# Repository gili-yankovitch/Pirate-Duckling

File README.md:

# Pirate-Duckling
Pirate Duckling is an ATTiny85 based Rubber Ducky clone. It is built with absolute minimal components in mind.

This PCB is manufactured with 1.2mm thickness. As USB ports are thicker than this, additional "USB Fatterners" are provided under hardware/ to add the necessary thickness to the USB part of the PCB.

## Prerequisits
### Software
Please install the following software to be able to flash software to the device:
* [Arduino SDK](https://www.arduino.cc/en/software)
* [Platformio](https://platformio.org/install/cli) or VScode with Platformio AddOn
* [Digispark Drivers](https://github.com/digistump/DigistumpArduino/releases/download/1.6.7/Digistump.Drivers.zip)
* [micronucleus](https://github.com/micronucleus/micronucleus/releases/download/v2.6/micronucleus-cli-master-882e7b4a-x86_64-MINGW64_NT-10.0-17763.zip) in case platformio's toolchain fails to find libusb0.dll, extract it under `%USERPROFILE%\.platformio\packages\tool-micronucleus`

### Hardware
All PCB specs are provided here under hardware/ and this can be easily manufactured as well as paneled for a larger volume. There are no special requirements for this board's manufacturing process.

#### Bill of Materials
| Quantity | Component Description | Mfr. No | Datasheet |
|----------|-----------------------|---------|-----------|
| 1 | SMD 1 kOhms 125 mW 0805 5% | RC0805JR-071KL | [Datasheet](https://www.mouser.co.il/datasheet/2/447/PYu_RC_Group_51_RoHS_L_11-1984063.pdf) |
| 1 | MCU AVR 8K FLSH 512B EE 512B SRAM ADC 5V | ATTiny85-20SU | [Datasheet](https://www.mouser.co.il/datasheet/2/268/Atmel_2586_AVR_8_bit_Microcontroller_ATtiny25_ATti-1315542.pdf) |
| 1 | 0.2W Intelligent external control surface mount SMD LED | SK6812Mini-E | [Datasheet](https://cdn-shop.adafruit.com/product-files/4960/4960_SK6812MINI-E_REV02_EN.pdf) |

# Software
## Software Building
Building the software is easy using platformio. Simply execute:
```
pio run --environment attiny85
```

### Software Flashing Using Arduino as an ISP using the broken-out pins
The [platformio.ini](platformio.ini) project is currently configured to be flashed using the Digispark bootloader, but it can also be flashed directly using an Arduino as an ISP. Simply connect the Arduino to the broken-out pin headers, uncomment the commented lines under platforio.ini and run:
```
pio run -t fuses
pio run --environment attiny85 --target upload
```

### Software Flashing Using the Digispark bootloader using the USB port
Flashing software using the USB port would require flashing the ATTiny85 with the bootloader [Attiny85.hex](https://github.com/gili-yankovitch/tinypad/blob/main/Digistump/bootloader/ATtiny85.hex) using the flash script [Burn_AT85_bootloader.bat](https://github.com/gili-yankovitch/tinypad/blob/main/Digistump/bootloader/Burn_AT85_bootloader.bat) which also sets the appropriate fuses at flash time.
```
%USERPROFILE%\.platformio\packages\arduino\tools\avrdude\6.3.0-arduino17\bin\avrdude.exe -C"%USERPROFILE%\.platformio\packages\arduino\tools\avrdude\6.3.0-arduino17\etc\avrdude.conf" -v -pattiny85 -cstk500v1 -P<COMPORT> -b19200 -Uflash:w:"ATtiny85.hex":i -U lfuse:w:0xe1:m -U hfuse:w:0xdd:m -U efuse:w:0xfe:m
```
* Don't forget to swap `<COMPORT>` to the appropriate COM port.

After that, you can build the software normally and flash it using the USB port. Run the following command and remember to only plug in the USB once the flash utility indicates it:
```
pio run --environment digispark-tiny --target upload
```

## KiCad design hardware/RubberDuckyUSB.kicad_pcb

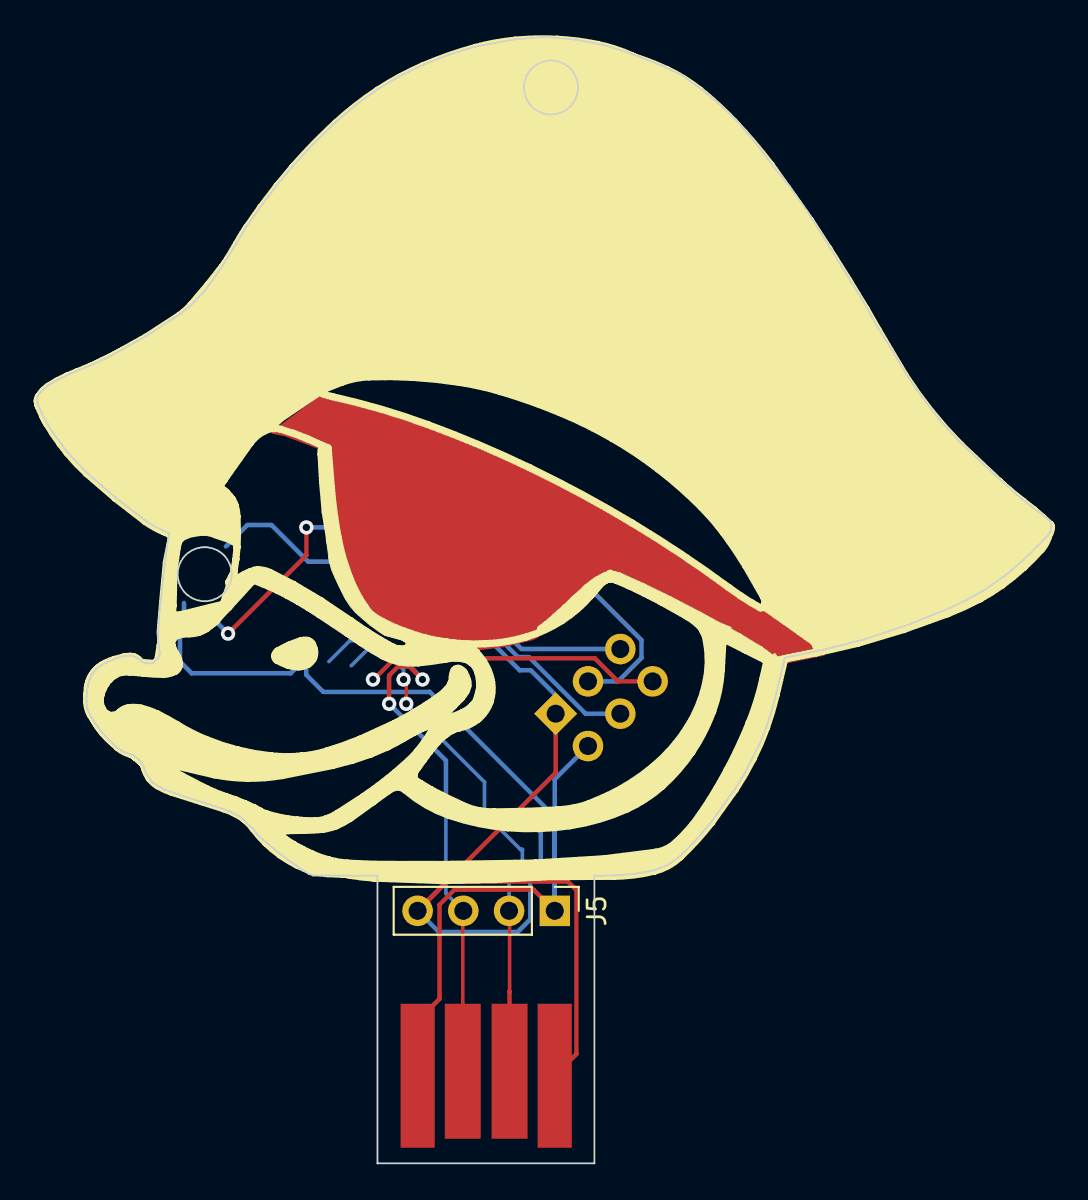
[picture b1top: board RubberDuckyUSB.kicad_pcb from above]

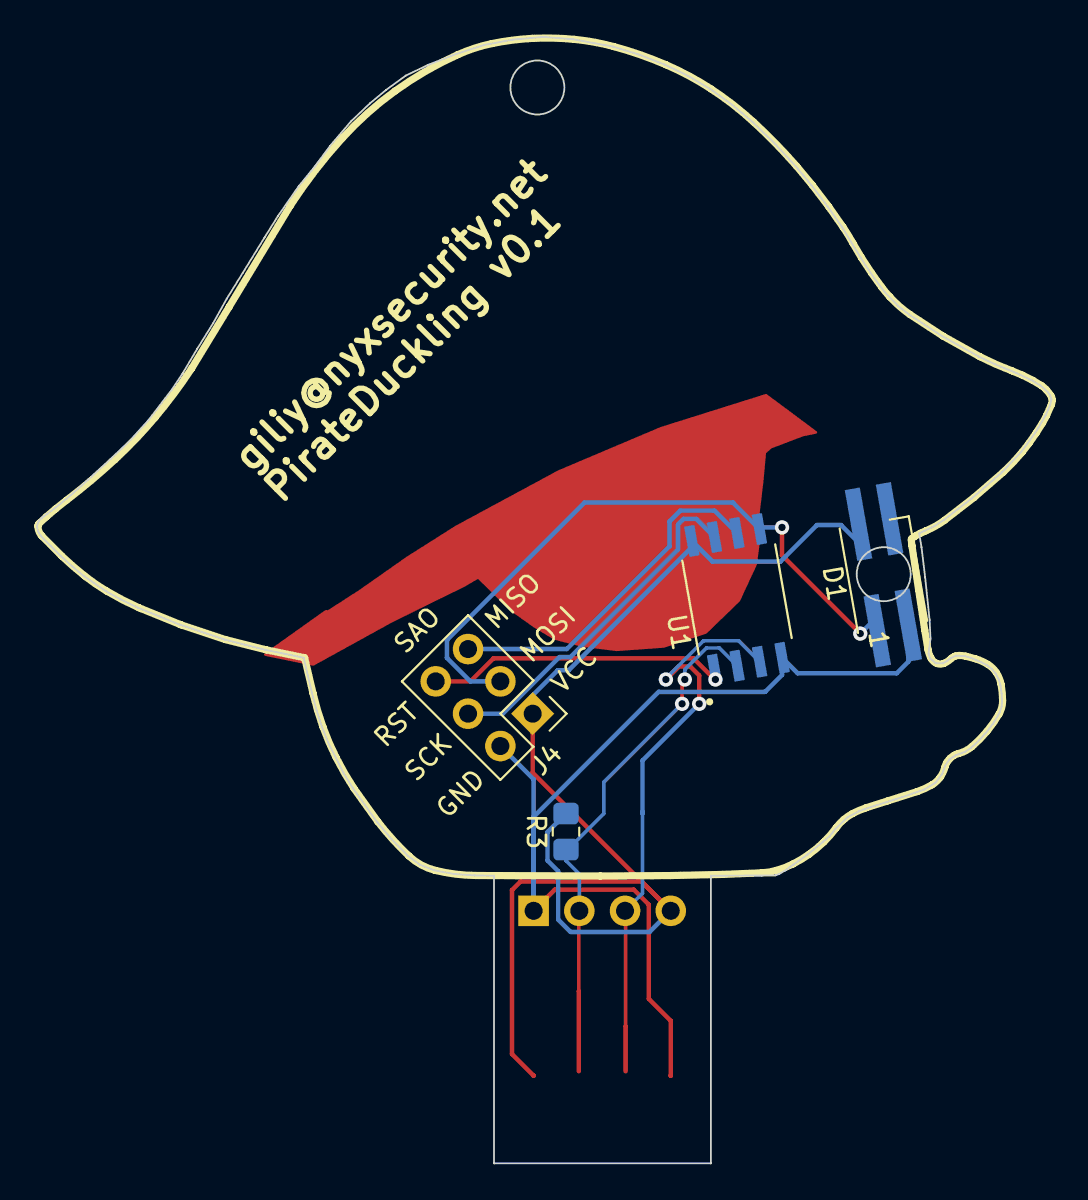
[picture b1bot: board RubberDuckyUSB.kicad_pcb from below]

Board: 2 copper layers, 56.4 x 62.6 mm, 6 parts (4 on the bottom side), 8 nets.

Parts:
D1: SK6812MINI; LED_SK6812MINI_PLCC4_3.5x3.5mm_P1.75mm
J1: USB_A; usb-PCB
J4: Conn_02x03_Odd_Even; PinHeader_2x03_P2.54mm_Vertical
J5: Conn_01x04_Pin; PinHeader_1x04_P2.54mm_Vertical
R3: R; R_0805_2012Metric_Pad1.20x1.40mm_HandSolder
U1: ATTINY85-20SU; SOIC127P798X216-8N

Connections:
Connector-D+: J1.3 (D+), J5.3, U1.3 (PB4)
Connector-D-: J1.2 (D-), J5.2, R3.1, U1.2 (PB3)
DATA: D1.3 (DIN), J4.3, U1.5 (PB0)
GND: D1.2 (VSS), J1.4 (GND), J4.2, J5.1, U1.4 (GND)
MISO: J4.5, U1.6 (PB1)
RST: J4.6, U1.1 (PB5)
SCK: J4.4, U1.7 (PB2)
Vcc: D1.4 (VDD), J1.1 (VBUS), J4.1, J5.4, R3.2, U1.8 (VCC)

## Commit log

2024-03-30 Initial commit with sources
2024-03-30 Revising hardware files
2024-03-30 Update README.md with PCB manufacturing thickness details
